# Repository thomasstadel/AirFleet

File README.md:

# AirFleet
Mobil kortlægning af luftkvalitet

## Formål
Formålet med dette projekt er at udvikle en IoT-løsning, der kan indsamle samples af luftkvalitet, herunder partikler, fugtighed, temperatur, CO2 baseret på GPS-lokation.

Enheden skal kunne installeres udvendigt (evt. ved luftindtag) på en bil.

Indsamlede data skal leveres til en webservice, hvor de skal gemmes i en database til efterfølgende analyse.

Der skal være et display på IoT-enheden, som giver mulighed for at informere føreren af bilen om luftkvalitet. 

Optimalt set vil IoT-enheden automatisk aktivere recirkulation i bilen ved lav luftkvalitet.

## Mappe-struktur

schematics/     Diagrammer og PCB layouts

display/        Kode relateret til display board

sensor/         Kode relateret til sensor board

stl/            STL-modeller af bokse

webserver/      Kode og database til webserver

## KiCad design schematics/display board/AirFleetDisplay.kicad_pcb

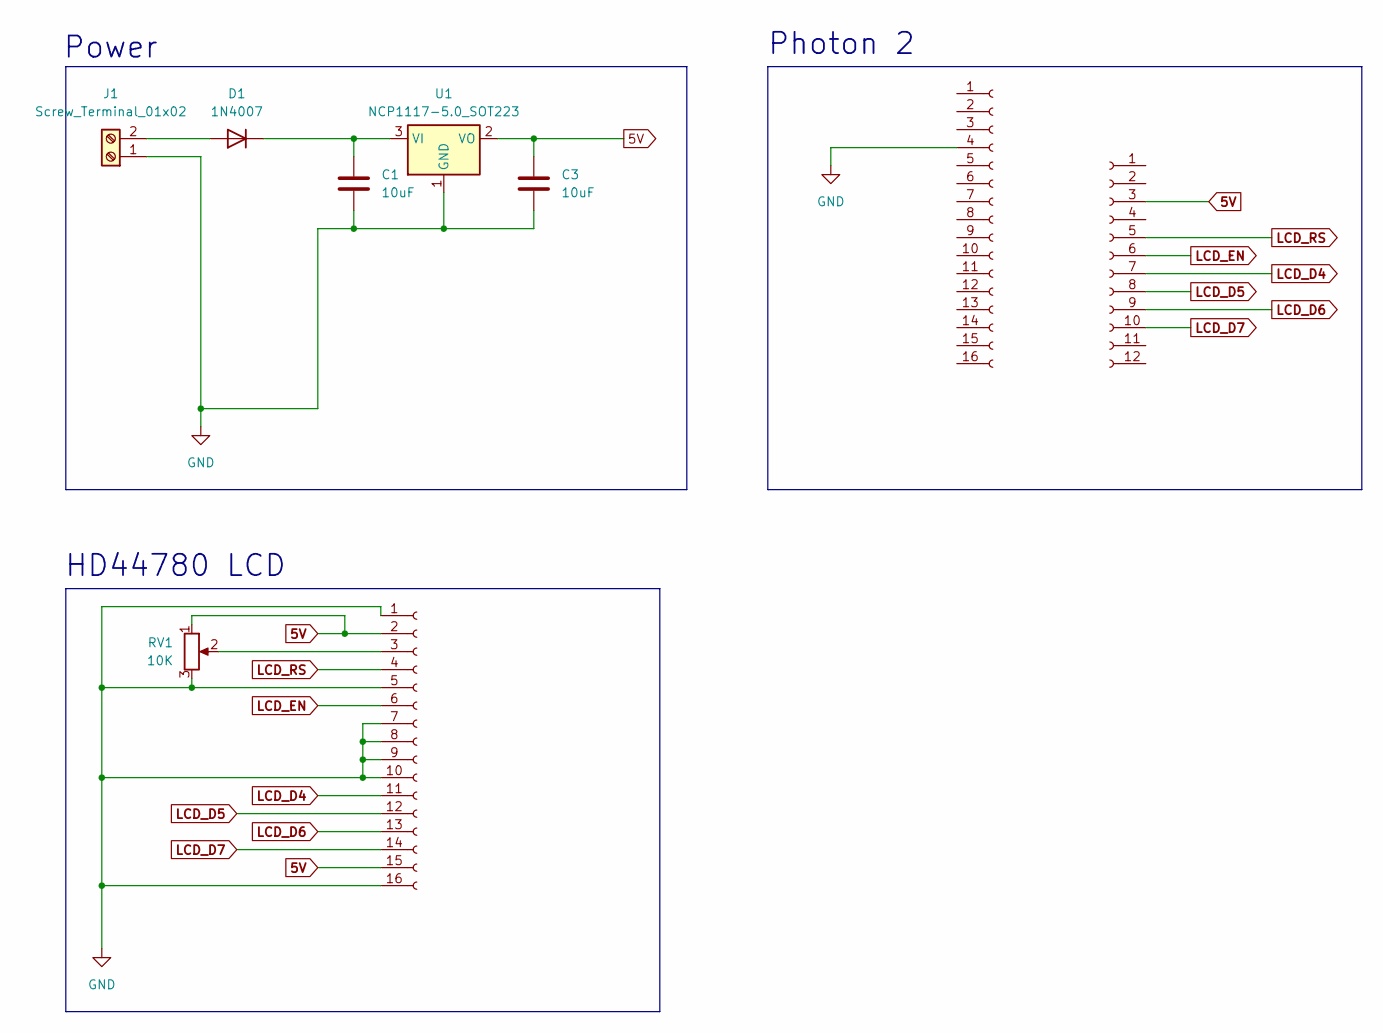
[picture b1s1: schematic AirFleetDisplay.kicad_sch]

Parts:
C1, C3: 10uF; C_1210_3225Metric_Pad1.33x2.70mm_HandSolder
D1: 1N4007; D_DO-15_P15.24mm_Horizontal
J1: Screw_Terminal_01x02; TerminalBlock_bornier-2_P5.08mm
J2, J4: Conn_01x16_Socket; PinSocket_1x16_P2.54mm_Vertical
J3: Conn_01x12_Socket; PinSocket_1x12_P2.54mm_Vertical
RV1: 10K; Potentiometer_Bourns_3386P_Vertical
U1: NCP1117-5.0_SOT223; SOT-223-3_TabPin2

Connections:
5V: C3.1, J3.3, J4.2, J4.15, RV1.1, U1.2 (VO)
GND: C1.2, C3.2, J1.1, J2.4, J4.1, J4.5, J4.7, J4.8, J4.9, J4.10, J4.16, RV1.3, U1.1 (GND)
LCD_D4: J3.7, J4.11
LCD_D5: J3.8, J4.12
LCD_D6: J3.9, J4.13
LCD_D7: J3.10, J4.14
LCD_EN: J3.6, J4.6
LCD_RS: J3.5, J4.4
unnamed: D1.2 (A), J1.2
unnamed: C1.1, D1.1 (K), U1.3 (VI)
unnamed: J4.3, RV1.2

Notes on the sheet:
HD44780 LCD
Photon 2
Power

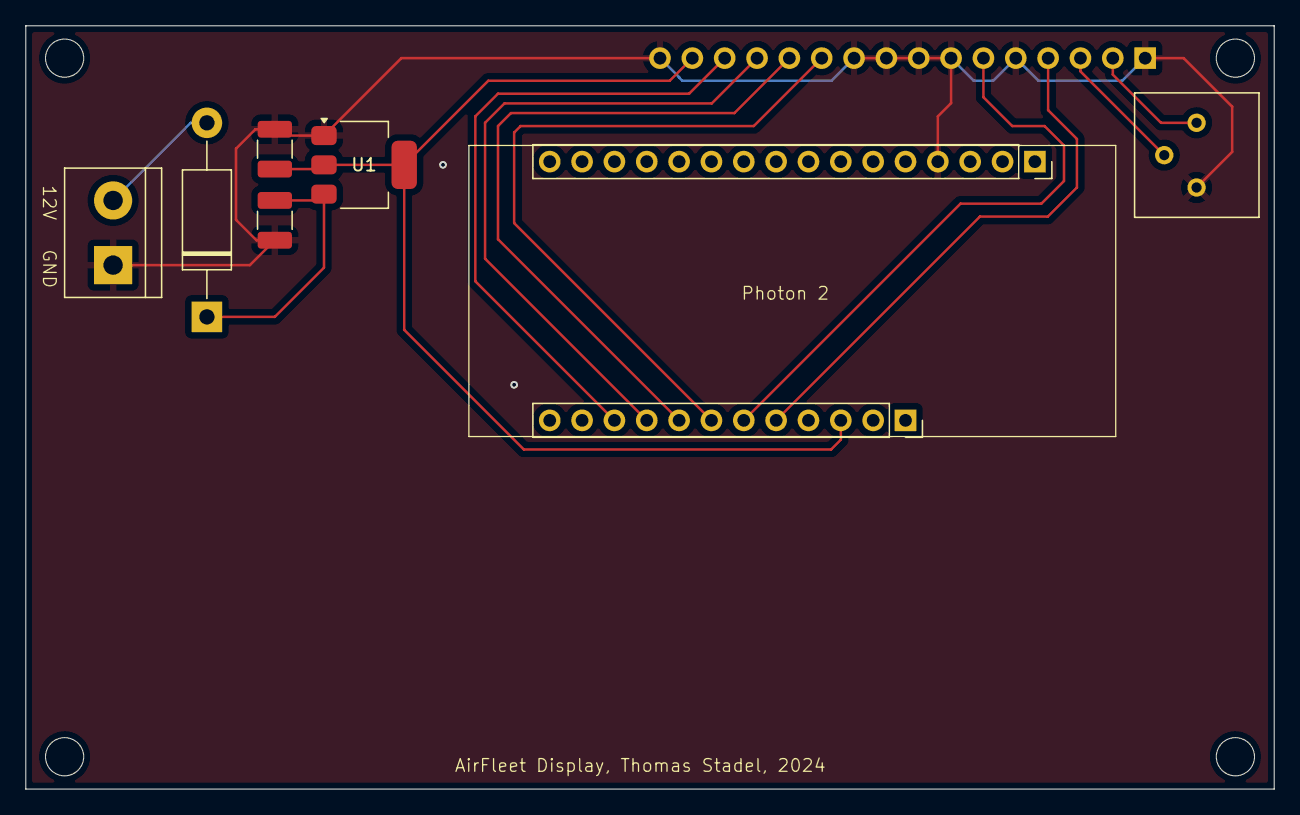
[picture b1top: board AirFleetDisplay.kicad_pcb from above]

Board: 2 copper layers, 98.0 x 59.9 mm, 9 parts (1 on the bottom side), 11 nets.

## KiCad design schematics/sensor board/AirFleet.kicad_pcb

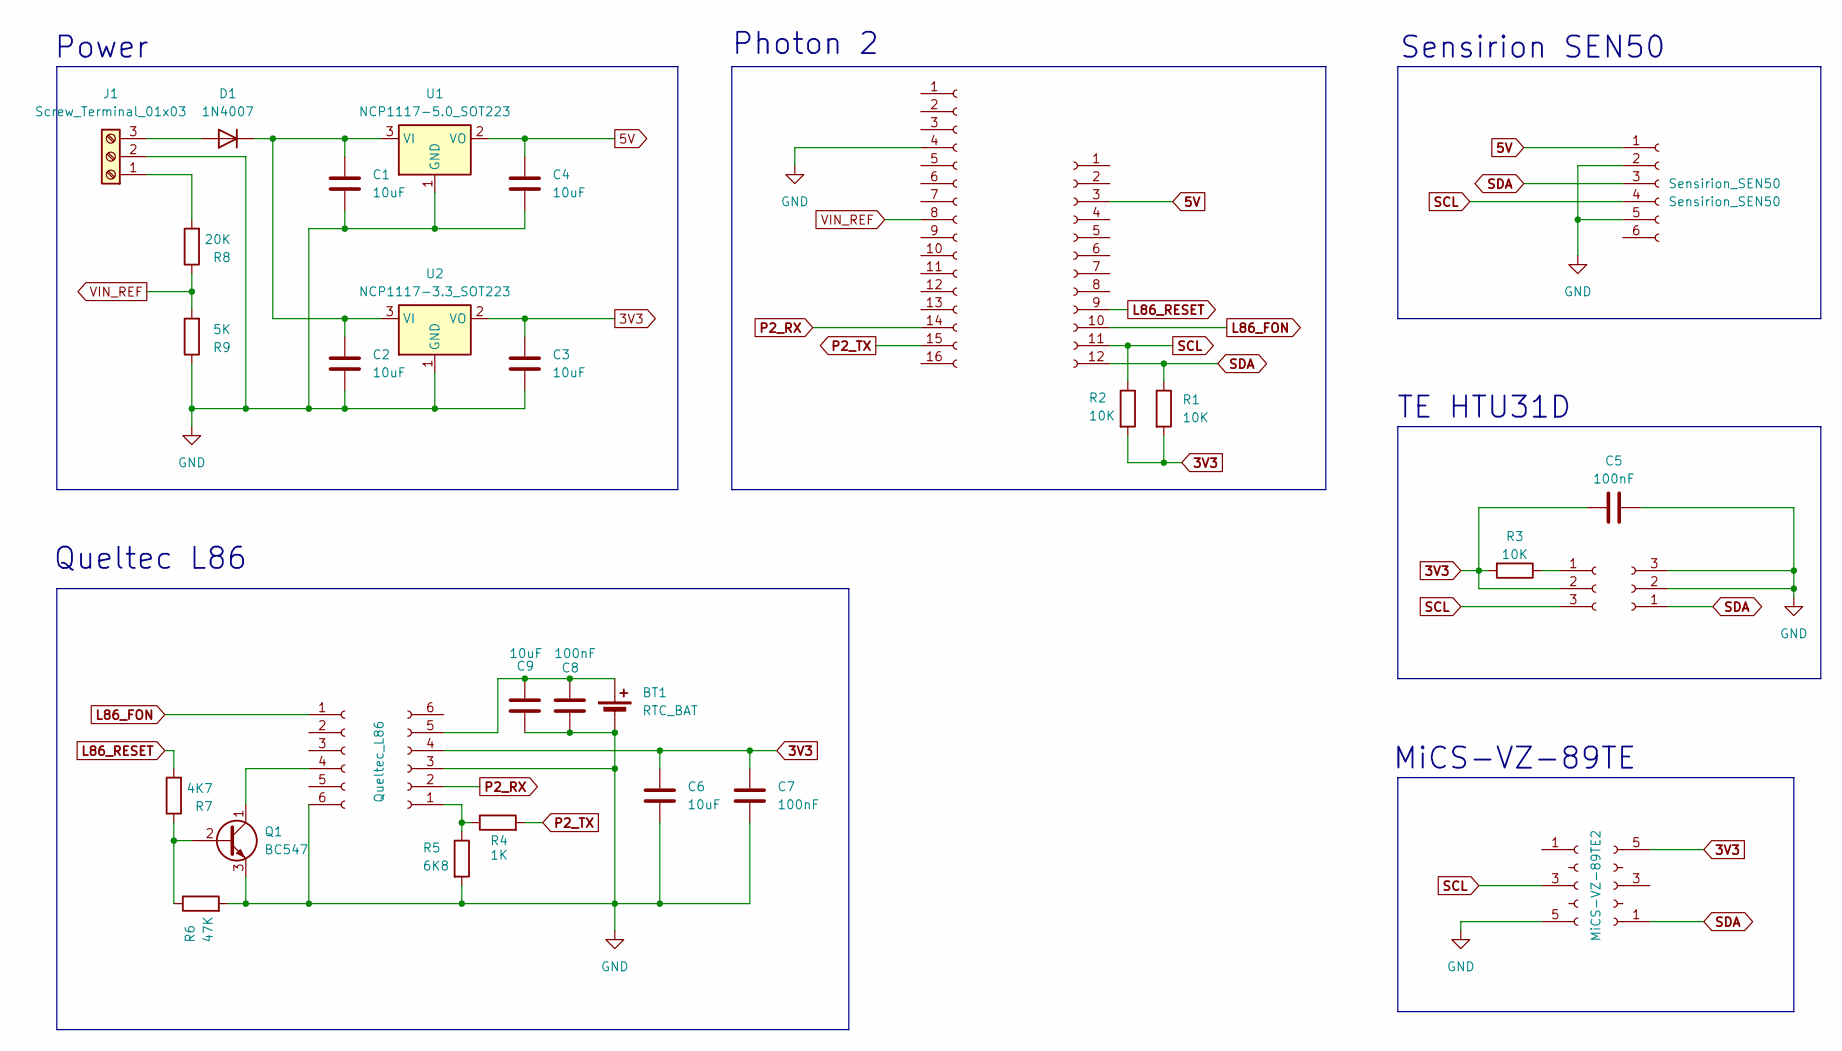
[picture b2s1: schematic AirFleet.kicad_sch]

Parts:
BT1: RTC_BAT; Battery_Panasonic_CR2032-HFN_Horizontal_CircularHoles
C1, C2, C3, C4, C6, C9: 10uF; C_1210_3225Metric_Pad1.33x2.70mm_HandSolder
C5, C7, C8: 100nF; C_1210_3225Metric_Pad1.33x2.70mm_HandSolder
D1: 1N4007; D_DO-15_P15.24mm_Horizontal
HTU31D1, HTU31D2: Conn_01x03_Socket; PinSocket_1x03_P2.54mm_Vertical
J1: Screw_Terminal_01x03; TerminalBlock_bornier-3_P5.08mm
J2: Conn_01x12_Socket; PinSocket_1x12_P2.54mm_Vertical
J3: Conn_01x16_Socket; PinSocket_1x16_P2.54mm_Vertical
J5: Conn_01x06_Socket; PinSocket_1x06_P2.54mm_Vertical
MiCS-VZ-89TE1, MiCS-VZ-89TE2: Conn_01x05_Socket; PinSocket_1x05_P2.54mm_Vertical
Q1: BC547; TO-92_Inline
Queltec_L86: Queltec_L86; PinSocket_1x06_P2.54mm_Vertical
R1, R2, R3: 10K; R_Axial_DIN0309_L9.0mm_D3.2mm_P12.70mm_Horizontal
R4: 1K; R_Axial_DIN0309_L9.0mm_D3.2mm_P12.70mm_Horizontal
R5: 6K8; R_Axial_DIN0309_L9.0mm_D3.2mm_P12.70mm_Horizontal
R6: 47K; R_Axial_DIN0309_L9.0mm_D3.2mm_P12.70mm_Horizontal
R7: 4K7; R_Axial_DIN0309_L9.0mm_D3.2mm_P12.70mm_Horizontal
R8: 20K; R_Axial_DIN0309_L9.0mm_D3.2mm_P12.70mm_Horizontal
R9: 5K; R_Axial_DIN0309_L9.0mm_D3.2mm_P12.70mm_Horizontal
Sensirion_SEN50: Sensirion_SEN50; PinSocket_1x06_P2.54mm_Vertical
U1: NCP1117-5.0_SOT223; SOT-223-3_TabPin2
U2: NCP1117-3.3_SOT223; SOT-223-3_TabPin2

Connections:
3V3: C3.1, C5.1, C6.1, C7.1, HTU31D1.2, MiCS-VZ-89TE2.5, Queltec_L86.4, R1.2, R2.2, R3.2, U2.2 (VO)
5V: C4.1, J2.3, Sensirion_SEN50.1, U1.2 (VO)
GND: BT1.2 (-), C1.2, C2.2, C3.2, C4.2, C5.2, C6.2, C7.2, C8.2, C9.2, HTU31D2.2, HTU31D2.3, J1.2, J3.4, J5.6, MiCS-VZ-89TE1.5, Q1.3 (E), Queltec_L86.3, R5.2, R6.2, R9.1, Sensirion_SEN50.2, Sensirion_SEN50.5, U1.1 (GND), U2.1 (GND)
L86_FON: J2.10, J5.1
L86_RESET: J2.9, R7.2
unnamed: BT1.1 (+), C8.1, C9.1, Queltec_L86.5
unnamed: D1.2 (A), J1.3
unnamed: C1.1, C2.1, D1.1 (K), U1.3 (VI), U2.3 (VI)
unnamed: HTU31D1.1, R3.1
unnamed: J1.1, R8.2
unnamed: J5.4, Q1.1 (C)
unnamed: Q1.2 (B), R6.1, R7.1
unnamed: Queltec_L86.1, R4.1, R5.1
P2_RX: J3.14, Queltec_L86.2
P2_TX: J3.15, R4.2
SCL: HTU31D1.3, J2.11, MiCS-VZ-89TE1.3, R2.1, Sensirion_SEN50.4
SDA: HTU31D2.1, J2.12, MiCS-VZ-89TE2.1, R1.1, Sensirion_SEN50.3
VIN_REF: J3.8, R8.1, R9.2

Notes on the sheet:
Sensirion SEN50
Queltec L86
TE HTU31D
MiCS-VZ-89TE
Photon 2
Power

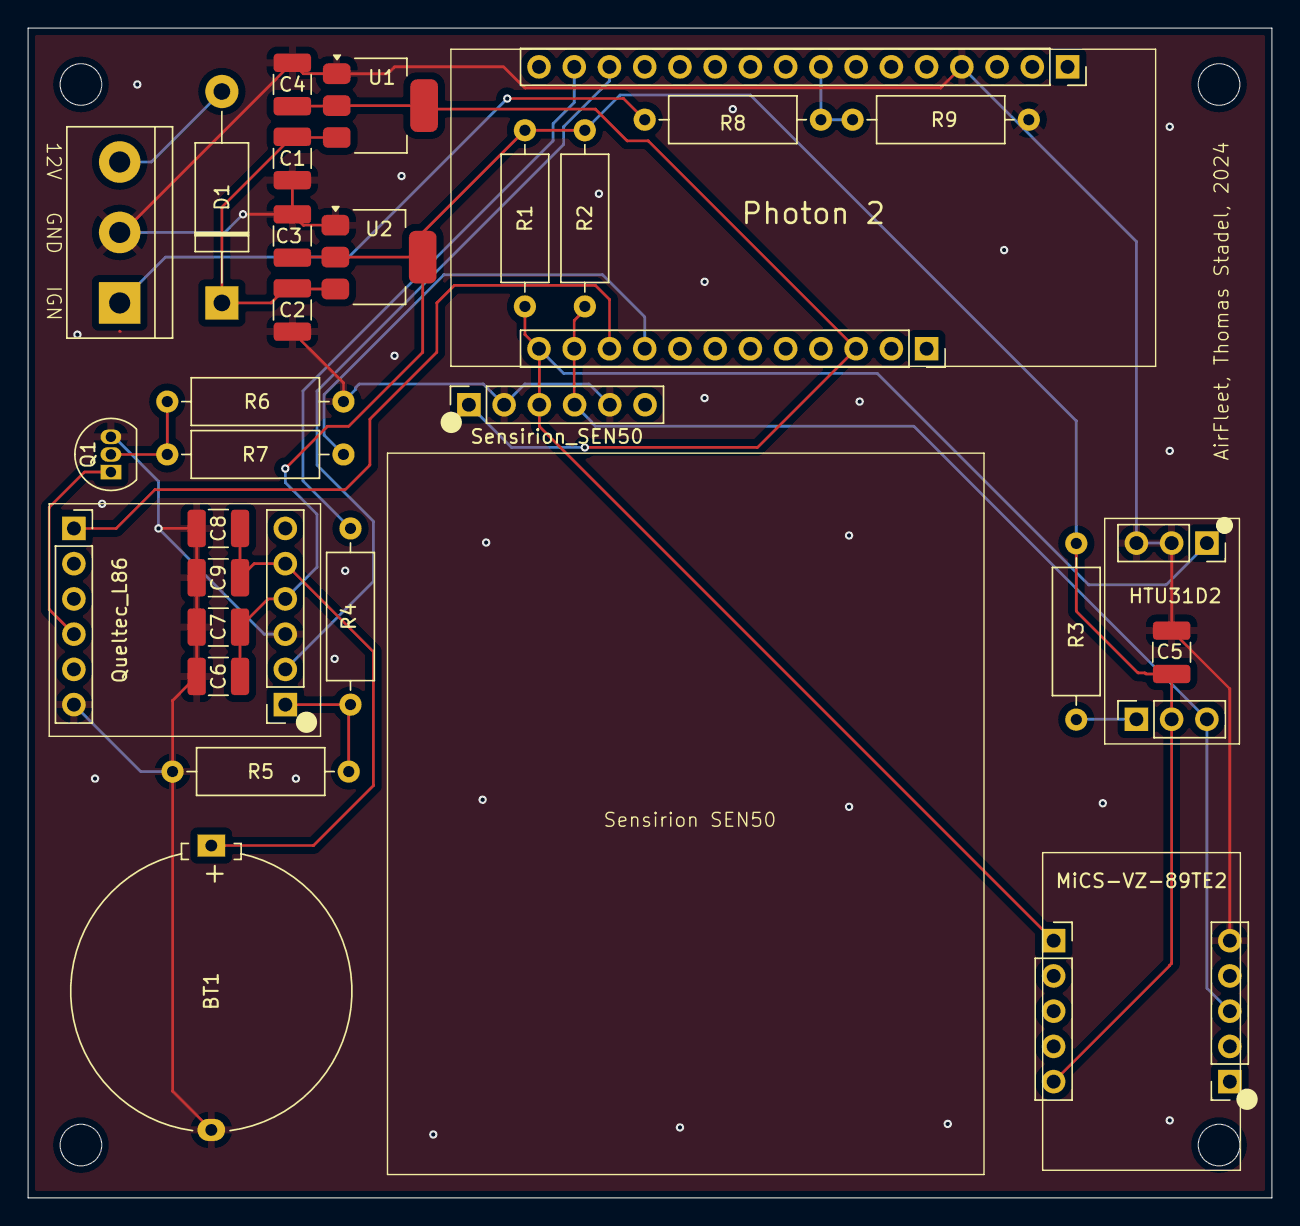
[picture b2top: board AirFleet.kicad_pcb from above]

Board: 2 copper layers, 89.7 x 84.3 mm, 33 parts (0 on the bottom side), 18 nets.

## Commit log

2024-09-22 README.md opdateret
2024-10-25 Added schematics for main and display board
2024-10-25 Opdateret README og organiseret mapper til source
2024-10-25 Opdateret PCB til display
2024-11-21 Opdateret kode til display
2024-11-22 Tilføjet driver til BLE enabled LCD og Sensirion sensor
2024-11-24 Tilføjet driver til HTU31, L86, MiCS
2024-11-24 Tilføjet Settings eksempel header fil
2024-11-27 Opdateret sensor, webserver, 3D print filer
2024-12-15 Opdatering af IOT kode og webservice
2024-12-17 Sidste rettelser
2024-12-19 Sidste version inden aflevering
